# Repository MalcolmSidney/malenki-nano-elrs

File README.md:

Malenki-Nano
=======

Malenki-Nano is a DC electronic speed controller and receiver for small robots. 

It is compatible with ExpressLRS protocol transmitters.
https://www.expresslrs.org/

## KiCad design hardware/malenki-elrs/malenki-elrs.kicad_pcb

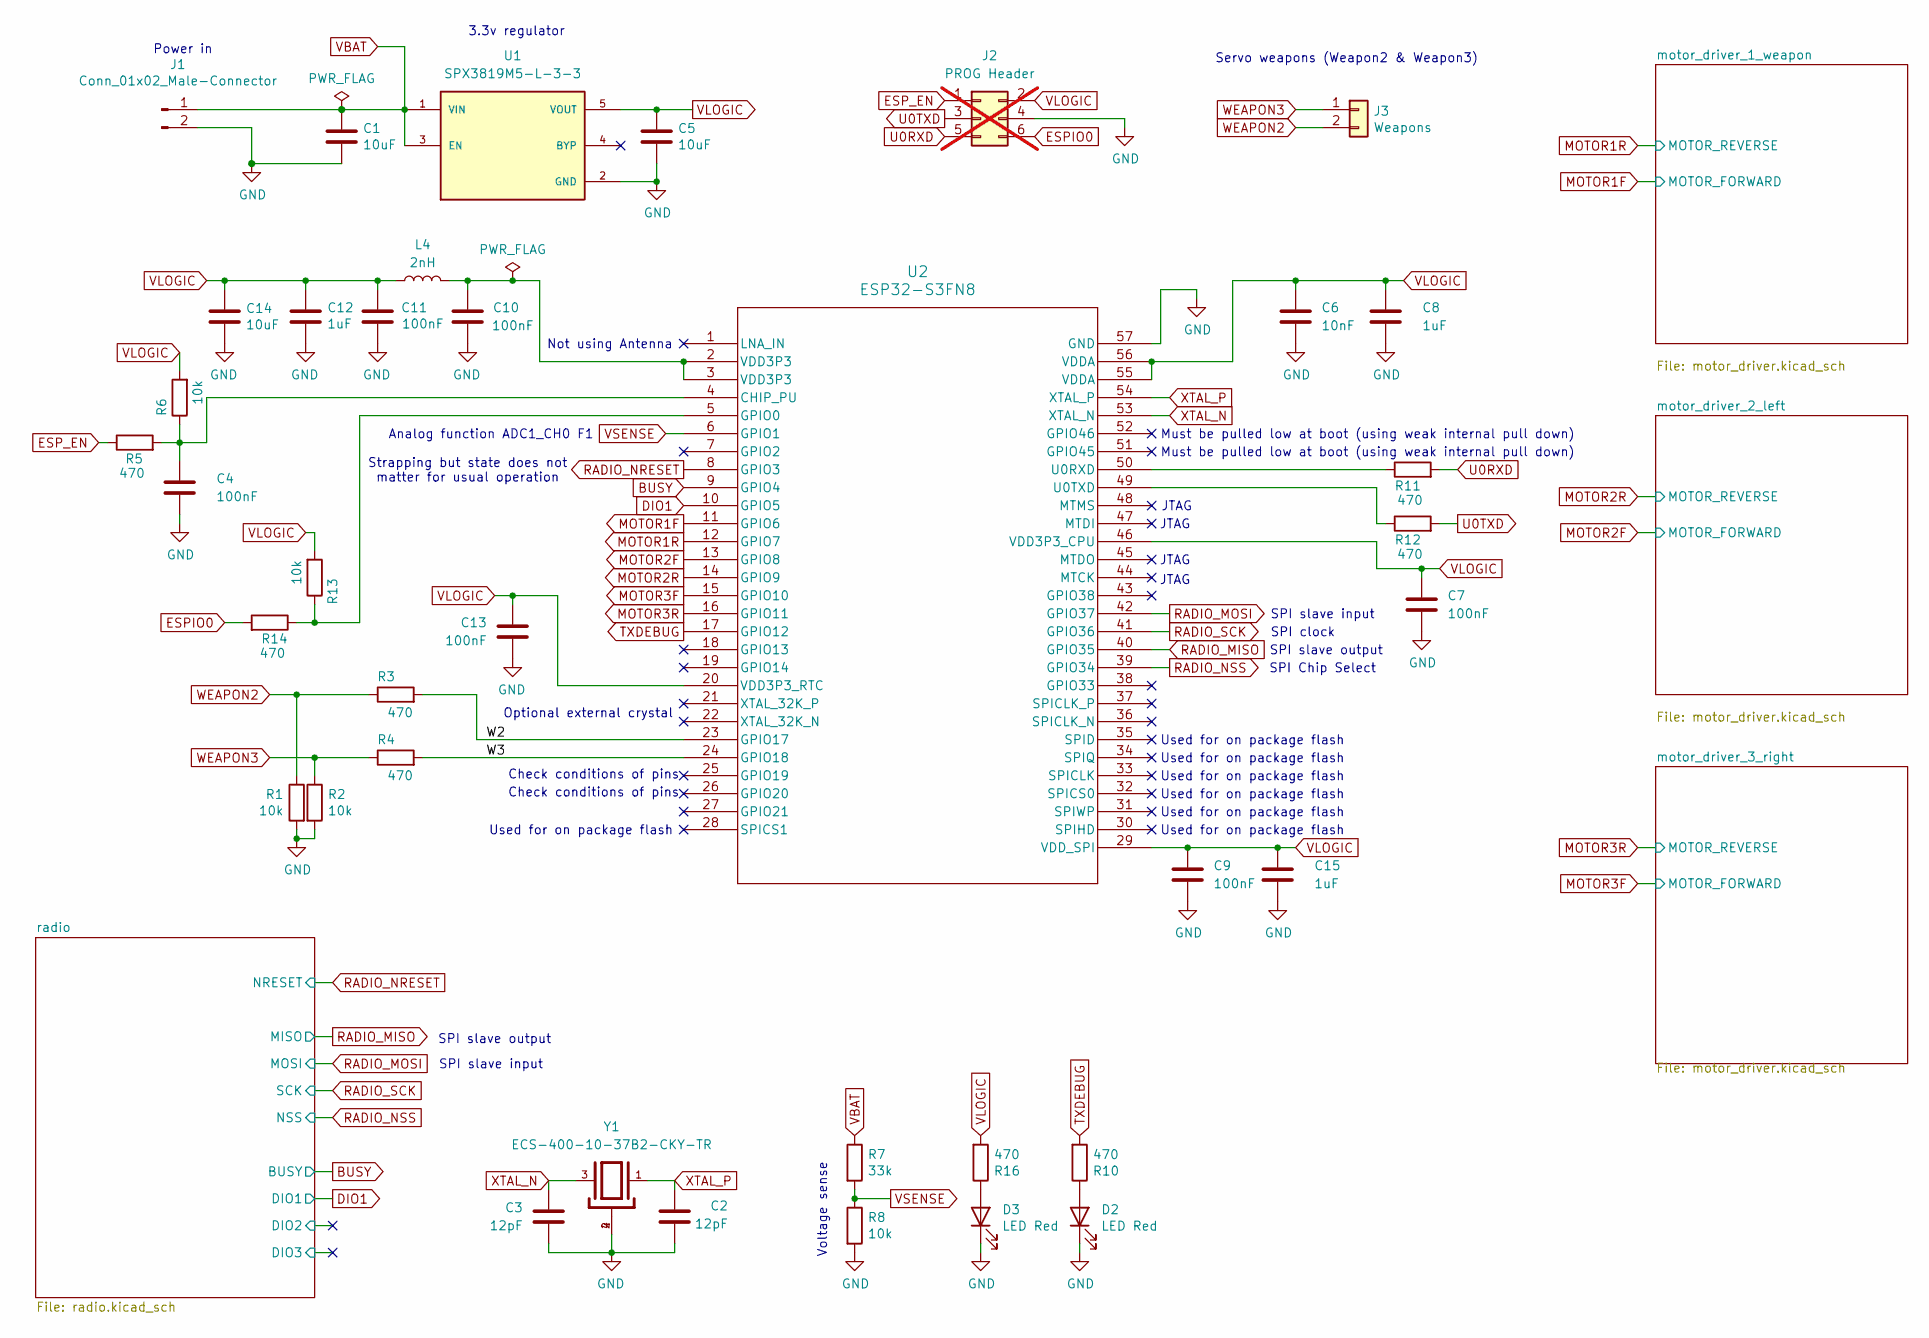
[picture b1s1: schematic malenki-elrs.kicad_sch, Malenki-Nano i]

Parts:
C1, C5, C14: 10uF; C_0603_1608Metric; LCSC Part # C96446
C2, C3: 12pF; C_0402_1005Metric; MPN 0402CG120J500NT; LCSC Part # C1547
C4, C7, C9, C10, C11, C13: 100nF; C_0402_1005Metric; MPN CL05B104KO5NNNC; LCSC Part # C1525
C6: 10nF; C_0402_1005Metric; LCSC Part # C15195
C8, C12, C15: 1uF; C_0402_1005Metric; MPN CL05A105KA5NQNC; LCSC Part # C52923
D2, D3: LED Red; LED_0402_1005Metric; MPN XL-1005SURC; LCSC Part # C25503345
J1: Conn_01x02_Male-Connector; malenkipower
J2: PROG Header; PinHeader_2x03_P1.27mm_Vertical; not fitted
J3: Weapons; wirepad_2
L4: 2nH; L_0402_1005Metric; MPN BLM15AG601SN1D; LCSC Part # C76884
R1, R2, R6, R8, R13: 10k; R_0402_1005Metric; Partnum 0402WGF1002TCE; LCSC Part # C25744
R3, R4, R5, R10, R11, R12, R14, R16: 470; R_0402_1005Metric; Partnum 0402WGF4700TCE; LCSC Part # C25117
R7: 33k; R_0402_1005Metric; Partnum 0402WGF3302TCE; LCSC Part # C25779
U1: SPX3819M5-L-3-3; SOT95P280X145-5N; PARTREV 2.0.5; LCSC Part # C9055
U2: ESP32-S3FN8; QFN56_7X7_EXP; LCSC Part # C2913196
Y1: ECS-400-10-37B2-CKY-TR; XTAL_ECS-400-10-37B2-CKY-TR; PARTREV 2021; LCSC Part # C5371760

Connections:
/W2: R3.2, U2.23 (GPIO17)
/W3: R4.2, U2.24 (GPIO18)
BUSY: U2.9 (GPIO4); also elsewhere on the board
DIO1: U2.10 (GPIO5); also elsewhere on the board
ESPIO0: J2.6, R14.2
ESP_EN: J2.1, R5.1
GND: C1.2, C2.2, C3.2, C4.2, C5.2, C6.2, C7.2, C8.2, C9.2, C10.2, C11.2, C12.2, C13.2, C14.2, C15.2, D2.1 (K), D3.1 (K), J1.2, J2.4, R1.2, R2.2, R8.2, U1.2 (GND), U2.57 (GND), Y1.2, Y1.4; also elsewhere on the board
MOTOR1F: U2.11 (GPIO6); also elsewhere on the board
MOTOR1R: U2.12 (GPIO7); also elsewhere on the board
MOTOR2F: U2.13 (GPIO8); also elsewhere on the board
MOTOR2R: U2.14 (GPIO9); also elsewhere on the board
MOTOR3F: U2.15 (GPIO10); also elsewhere on the board
MOTOR3R: U2.16 (GPIO11); also elsewhere on the board
unnamed: C10.1, L4.2, U2.2 (VDD3P3), U2.3 (VDD3P3)
unnamed: D2.2 (A), R10.1
unnamed: D3.2 (A), R16.1
unnamed: C4.1, R5.2, R6.1, U2.4 (CHIP_PU)
unnamed: R13.1, R14.1, U2.5 (GPIO0)
unnamed: R11.1, U2.50 (U0RXD)
unnamed: R12.1, U2.49 (U0TXD)
RADIO_MISO: U2.40 (GPIO35); also elsewhere on the board
RADIO_MOSI: U2.42 (GPIO37); also elsewhere on the board
RADIO_NRESET: U2.8 (GPIO3); also elsewhere on the board
RADIO_NSS: U2.39 (GPIO34); also elsewhere on the board
RADIO_SCK: U2.41 (GPIO36); also elsewhere on the board
TXDEBUG: R10.2, U2.17 (GPIO12)
U0RXD: J2.5, R11.2
U0TXD: J2.3, R12.2
VBAT: C1.1, J1.1, R7.1, U1.1 (VIN), U1.3 (EN); also elsewhere on the board
VLOGIC: C5.1, C6.1, C7.1, C8.1, C9.1, C11.1, C12.1, C13.1, C14.1, C15.1, J2.2, L4.1, R6.2, R13.2, R16.2, U1.5 (VOUT), U2.20 (VDD3P3_RTC), U2.29 (VDD_SPI), U2.46 (VDD3P3_CPU), U2.55 (VDDA), U2.56 (VDDA); also elsewhere on the board
VSENSE: R7.2, R8.1, U2.6 (GPIO1)
WEAPON2: J3.2, R1.1, R3.1
WEAPON3: J3.1, R2.1, R4.1
XTAL_N: C3.1, U2.53 (XTAL_N), Y1.3
XTAL_P: C2.1, U2.54 (XTAL_P), Y1.1

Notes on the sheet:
JTAG
Voltage sense
Must be pulled low at boot (using weak internal pull down)
SPI slave input
Power in
Servo weapons (Weapon2 & Weapon3)
Used for on package flash
SPI Chip Select
SPI slave output
Analog function ADC1_CH0 F1
Not using Antenna
SPI clock
Check conditions of pins
Strapping but state does not matter for usual operation
Optional external crystal
3.3v regulator

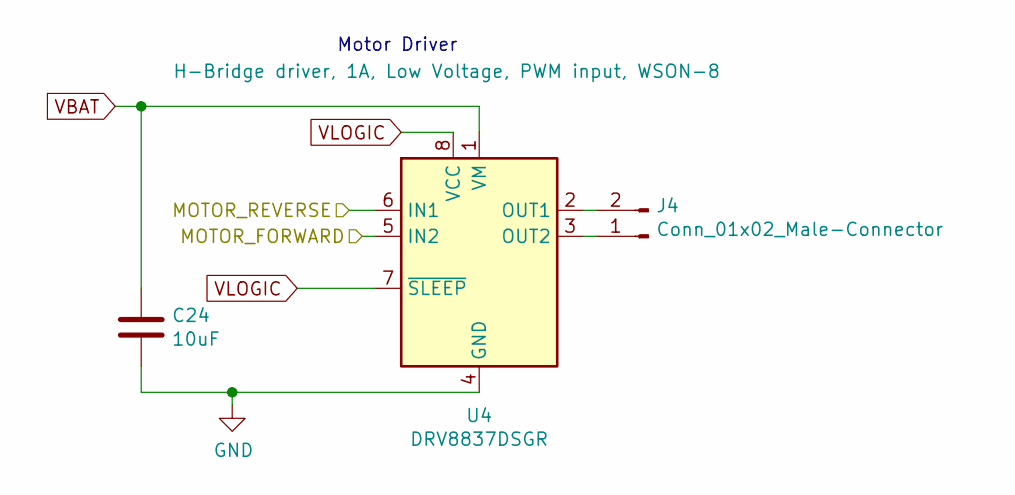
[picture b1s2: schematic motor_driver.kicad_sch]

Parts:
C24: 10uF; C_0603_1608Metric; LCSC Part # C96446
J4: Conn_01x02_Male-Connector; PinHeader_1x02_P2.54mm_BIG1
U4: DRV8837DSGR; WSON-8-1EP_2x2mm_P0.5mm_EP0.9x1.6mm; MPN DRV8837DSGR; LCSC Part # C39159

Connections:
GND: C24.2, U4.4 (GND), U4.9 (GND); also elsewhere on the board
MOTOR1F: U4.5 (IN2); also elsewhere on the board
MOTOR1R: U4.6 (IN1); also elsewhere on the board
unnamed: J4.1, U4.3 (OUT2)
unnamed: J4.2, U4.2 (OUT1)
VBAT: C24.1, U4.1 (VM); also elsewhere on the board
VLOGIC: U4.7 (~SLEEP), U4.8 (VCC); also elsewhere on the board

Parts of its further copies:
C25, C26: 10uF; C_0603_1608Metric; LCSC Part # C96446
J5, J6: Conn_01x02_Male-Connector; PinHeader_1x02_P2.54mm_BIG1
U5, U6: DRV8837DSGR; WSON-8-1EP_2x2mm_P0.5mm_EP0.9x1.6mm; MPN DRV8837DSGR; LCSC Part # C39159

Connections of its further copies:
GND: C25.2, C26.2, U5.4 (GND), U5.9 (GND), U6.4 (GND), U6.9 (GND); also elsewhere on the board
MOTOR2F: U5.5 (IN2); also elsewhere on the board
MOTOR2R: U5.6 (IN1); also elsewhere on the board
MOTOR3F: U6.5 (IN2); also elsewhere on the board
MOTOR3R: U6.6 (IN1); also elsewhere on the board
unnamed: J5.1, U5.3 (OUT2)
unnamed: J5.2, U5.2 (OUT1)
unnamed: J6.1, U6.3 (OUT2)
unnamed: J6.2, U6.2 (OUT1)
VBAT: C25.1, C26.1, U5.1 (VM), U6.1 (VM); also elsewhere on the board
VLOGIC: U5.7 (~SLEEP), U5.8 (VCC), U6.7 (~SLEEP), U6.8 (VCC); also elsewhere on the board

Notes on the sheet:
Motor Driver

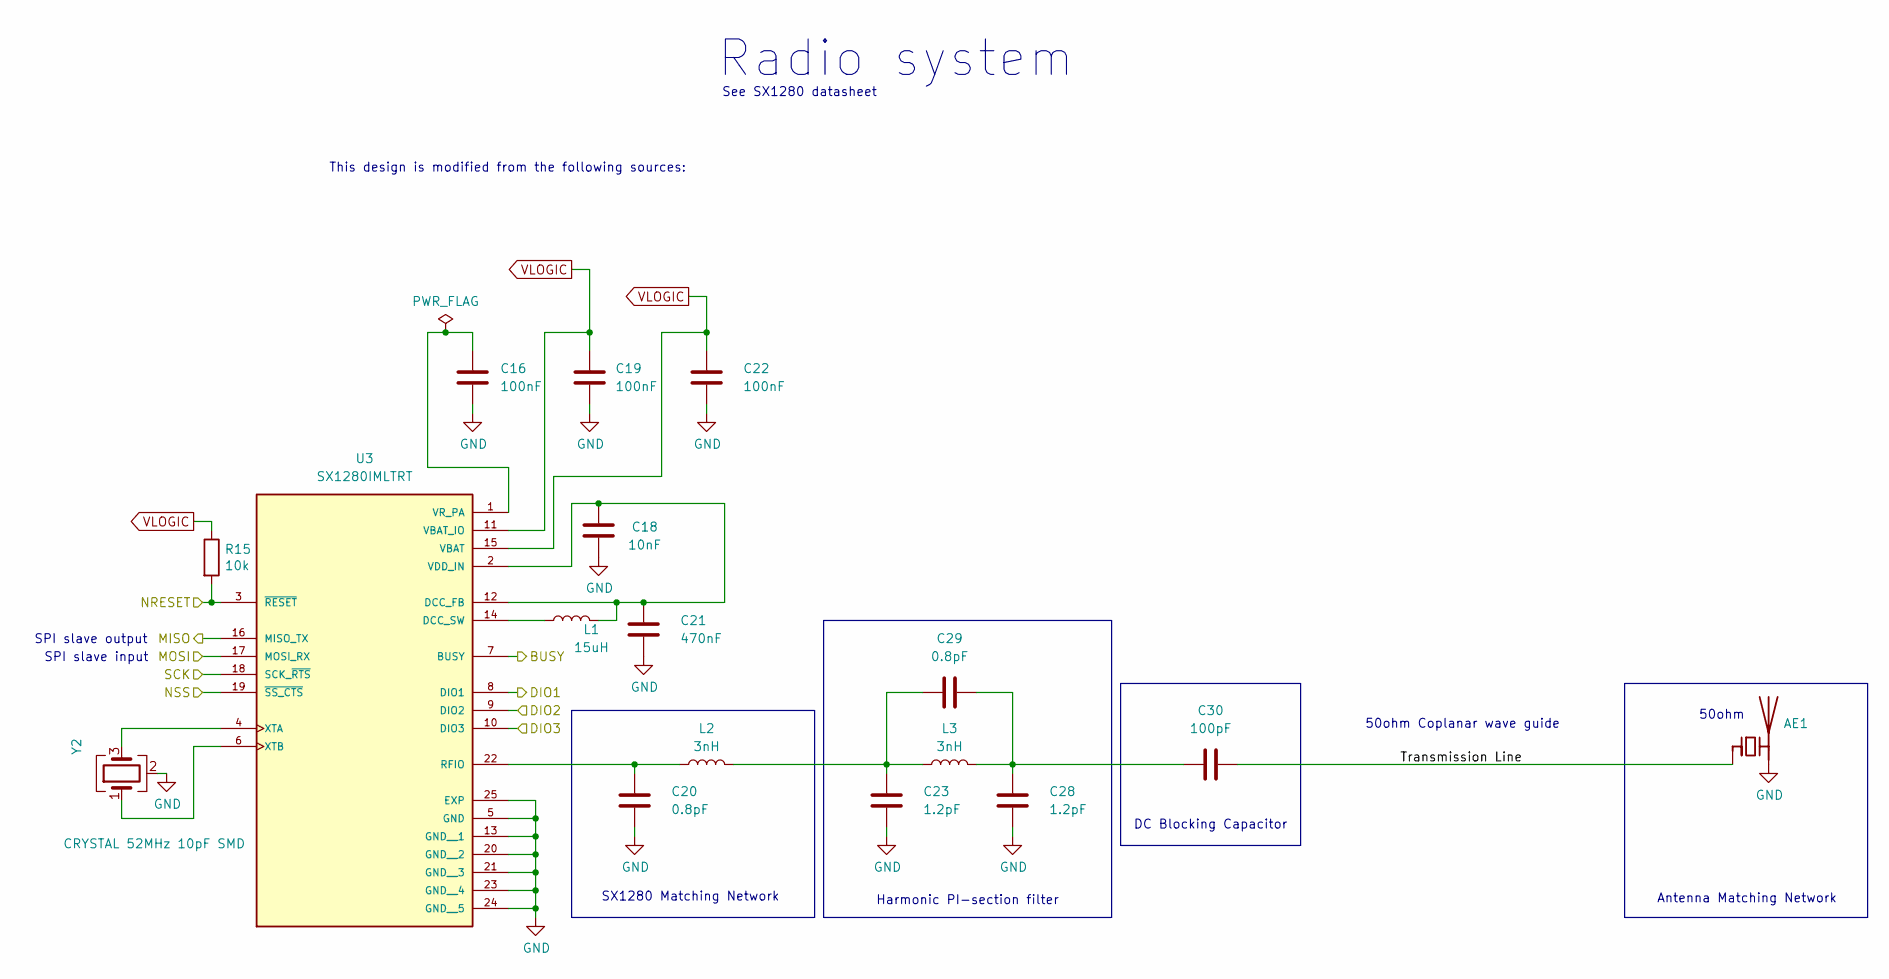
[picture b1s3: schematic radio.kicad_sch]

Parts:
AE1: malenki_antenna
C16, C19, C22: 100nF; C_0402_1005Metric; MPN CL05B104KO5NNNC; LCSC Part # C1525
C18: 10nF; C_0402_1005Metric; LCSC Part # C15195
C20, C29: 0.8pF; C_0402_1005Metric; MPN GRM1555C1HR80BA01D; LCSC Part # C76988
C21: 470nF; C_0402_1005Metric; MPN CL05A474KP5NNNC; LCSC Part # C47339
C23, C28: 1.2pF; C_0402_1005Metric; MPN GJM1555C1H1R2WB01D; LCSC Part # C76899
C30: 100pF; C_0402_1005Metric; MPN GRM1555C1H101JA01D; LCSC Part # C77177
L1: 15uH; L_0805_2012Metric; LCSC Part # C383402
L2, L3: 3nH; L_0402_1005Metric; MPN LQW15AN3N0B80D; LCSC Part # C2041661
R15: 10k; R_0402_1005Metric; Partnum 0402WGF1002TCE; LCSC Part # C25744
U3: SX1280IMLTRT; XCVR_SX1280IMLTRT; PARTREV 3.3; LCSC Part # C125969
Y2: CRYSTAL 52MHz 10pF SMD; Crystal_SMD_2520-4Pin_2.5x2.0mm; MPN Q24FA20H0051200; LCSC Part # C49253546

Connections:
/radio/DIO2: U3.9 (DIO2)
/radio/DIO3: U3.10 (DIO3)
/radio/Transmission Line: AE1.1 (FEED), C30.2
BUSY: U3.7 (BUSY); also elsewhere on the board
DIO1: U3.8 (DIO1); also elsewhere on the board
GND: AE1.2 (PCB_Trace), C16.2, C18.2, C19.2, C20.2, C21.2, C22.2, C23.2, C28.2, U3.5 (GND), U3.13 (GND__1), U3.20 (GND__2), U3.21 (GND__3), U3.23 (GND__4), U3.24 (GND__5), U3.25 (EXP), Y2.2 (G), Y2.4 (G); also elsewhere on the board
unnamed: C23.1, C29.1, L2.2, L3.1
unnamed: C28.1, C29.2, C30.1, L3.2
unnamed: C18.1, C21.1, L1.2, U3.2 (VDD_IN), U3.12 (DCC_FB)
unnamed: L1.1, U3.14 (DCC_SW)
unnamed: C20.1, L2.1, U3.22 (RFIO)
unnamed: C16.1, U3.1 (VR_PA)
unnamed: U3.4 (XTA), Y2.3
unnamed: U3.6 (XTB), Y2.1
RADIO_MISO: U3.16 (MISO_TX); also elsewhere on the board
RADIO_MOSI: U3.17 (MOSI_RX); also elsewhere on the board
RADIO_NRESET: R15.2, U3.3 (~RESET); also elsewhere on the board
RADIO_NSS: U3.19 (~SS_CTS); also elsewhere on the board
RADIO_SCK: U3.18 (SCK_~RTS); also elsewhere on the board
VLOGIC: C19.1, C22.1, R15.1, U3.11 (VBAT_IO), U3.15 (VBAT); also elsewhere on the board

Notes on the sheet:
50ohm Coplanar wave guide
Radio system
DC Blocking Capacitor
Harmonic PI-section filter
SPI slave input
Antenna Matching Network
See SX1280 datasheet
SPI slave output
This design is modified from the following sources:
SX1280 Matching Network
50ohm

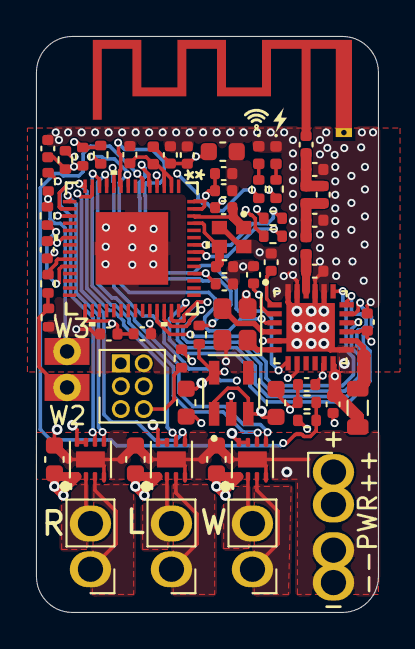
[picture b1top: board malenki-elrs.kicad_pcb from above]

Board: 4 copper layers, 19.0 x 32.0 mm, 64 parts (0 on the bottom side), 50 nets.

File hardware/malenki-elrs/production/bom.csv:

Designator,Footprint,Quantity,Value,LCSC Part #
"C1, C14, C24, C25, C26, C5",0603,6,10uF,C96446
"C10, C11, C13, C16, C19, C22, C4, C7, C9",0402,9,100nF,C1525
"C12, C15, C8",0402,3,1uF,C52923
"C18, C6",0402,2,10nF,C15195
"C2, C3",0402,2,12pF,C1547
"C20, C29",0402,2,0.8pF,C76988
C21,0402,1,470nF,C47339
"C23, C28",0402,2,1.2pF,C76899
C30,0402,1,100pF,C77177
"D2, D3",0402,2,LED Red,C25503345
L1,0805,1,15uH,C383402
"L2, L3",0402,2,3nH,C2041661
L4,0402,1,2nH,C76884
"R1, R13, R15, R2, R6, R8",0402,6,10k,C25744
"R10, R11, R12, R14, R16, R3, R4, R5",0402,8,470,C25117
R7,0402,1,33k,C25779
U1,SOT95P280X145-5N,1,SPX3819M5-L-3-3,C9055
U2,QFN56_7X7_EXP,1,ESP32-S3FN8,C2913196
U3,XCVR_SX1280IMLTRT,1,SX1280IMLTRT,C125969
"U4, U5, U6",WSON-8-1EP_2x2mm_P0.5mm_EP0.9x1.6mm,3,DRV8837DSGR,C39159
Y1,XTAL_ECS-400-10-37B2-CKY-TR,1,ECS-400-10-37B2-CKY-TR,C5371760
Y2,Crystal_SMD_2520-4Pin_2.5x2.0mm,1,CRYSTAL 52MHz 10pF SMD,C49253546

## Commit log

2026-04-23 Creating elrs folder
2026-04-24 Adding elrs rf chip and esp32 micro controller.
2026-04-24 Switching to developer branch
2026-04-24 Finalised initial SX1280 schematics, started ESP32 schematic, replace Vreg in schematic
2026-04-25 Completed preliminary schematics
2026-04-25 Placing components for ESP and SX1280
2026-04-25 Preliminary board layout complete
    Awaiting reviewers and preparations for PCBA
2026-04-26 Added datasheets for major components
2026-04-28 minor changes ready for final checks
2026-04-28 Adding ESP32-U4WDH
    Found that not enough pins were usable on the esp32-c4 as the internal flash memory still using the SPI bus pins available which I did not initially know about :(
2026-04-28 Changed microcontroller and completed schematic
    Changed micro controller to the esp32-s3FN8, for more available pins.
    Complete schematic.
    Changed to pcb antenna.
    Completed initial placement of all components on PCB.
2026-04-29 Changed component parts to match JLCPCB basic parts
    Saving assembly cost by changing all possible components to JLCPCB basic part, and reducing number of separate components where possible. Started trace placement
2026-04-30 Completed trace placement
2026-05-02 Updating datasheets
2026-05-02 Finalised pcb by placing ground stitching via's
2026-05-04 Generated production files
2026-05-05 Updated production files
2026-05-05 Added power led, and images
2026-05-06 Updated production files ready for ordering
2026-05-07 Change compatibility from AFHDS-2A to ExpressLRS
    Updated compatibility information for transmitters.
2026-05-07 added application note for antenna and final updated production files.
2026-05-07 Updated silkscreen logos
2026-06-04 Updated schematic
